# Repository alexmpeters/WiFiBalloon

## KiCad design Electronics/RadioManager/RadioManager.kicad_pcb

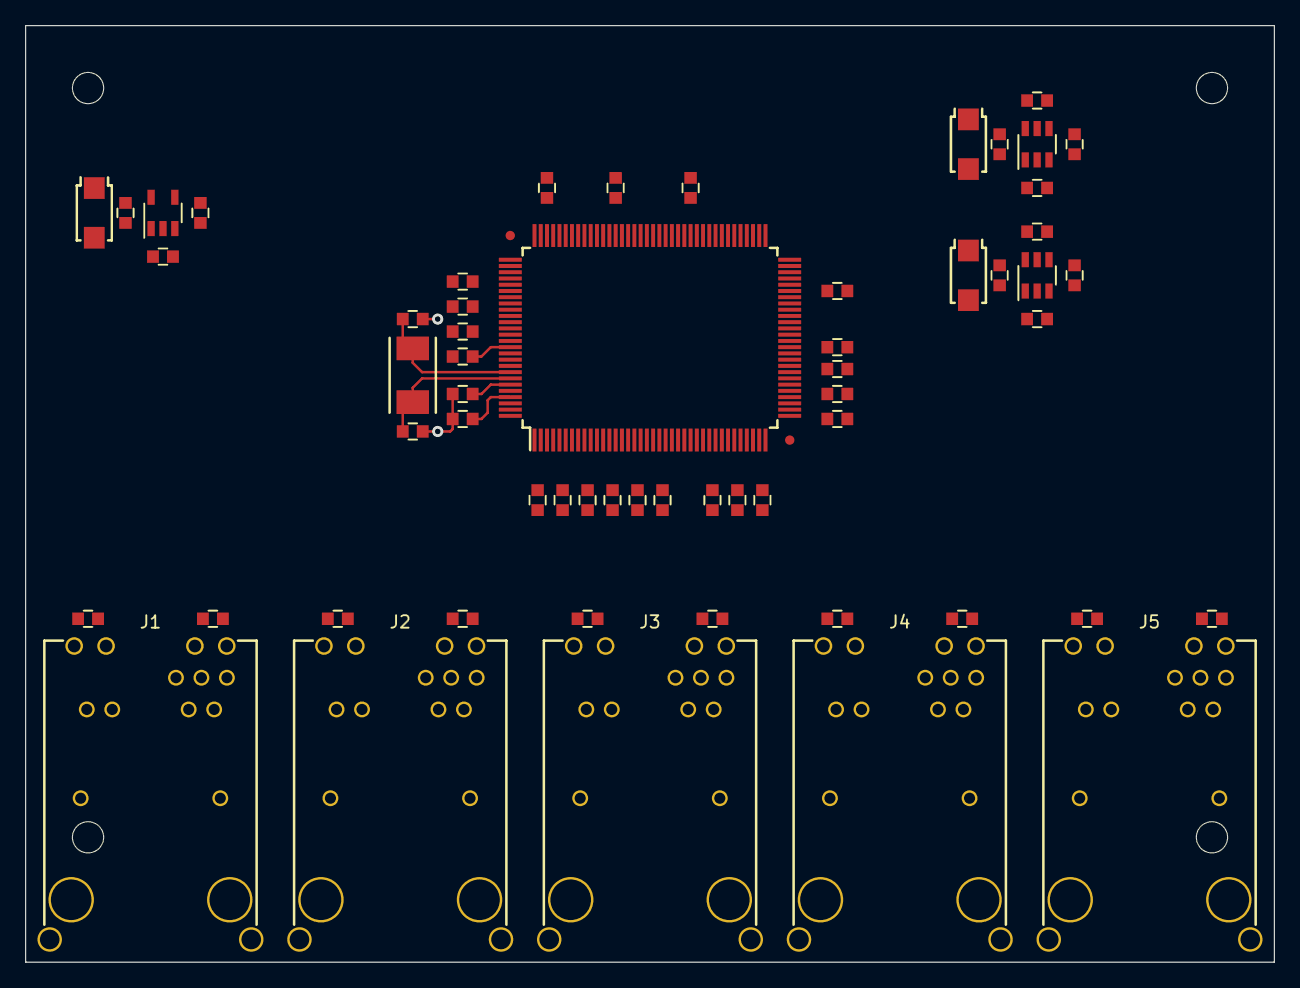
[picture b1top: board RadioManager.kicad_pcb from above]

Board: 2 copper layers, 100.0 x 75.0 mm, 63 parts (0 on the bottom side), 64 nets.

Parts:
C1, C2, C3, C4, C5, C6, C7, C8, C9, C10, C11, C12, C13, C14, C15, C16, C30: C; CAPC1608-N
C22, C23: 33pF; CAPC1608-N
C26, C27: 10000pF; CAPC1608-N
D1, D3, D4: CDBA140; SODFL5126-N
J1, J2, J3, J4, J5: RJ45-MAG-LED; CONN-0826-1L1T-57-F
MECH-JIG250, MECH-JIG250#2, MECH-JIG250#3, MECH-JIG250#4: VAL**; MECH-JIG250
R1, R2, R3, R10, R11, R16, R17, R18, R19, R20, R21, R22, R23, R24, R25: R; RESC1608-N
R4, R6, R7, R8, R9: 10k; RESC1608-N
R5: 3.01k; RESC1608-N
R12: 49.9k; RESC1608-N
R13: 15.8k; RESC1608-N
R14: 80.6k; RESC1608-N
R15: 64.2k; RESC1608-N
U1: KSZ8995FQI; QFP50P2320X1720-128N
U2: SC4503; SOT95P280-5N
U3, U4: AOZ1280; SOT95P280-6N
X1: 25MHz; XTAL-2SMD-60x35

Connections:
+1.8V: C1.1, C2.1, C4.1, C5.1, C7.1, C8.1, C10.1, C11.1, C13.1, C15.1, U1.3, U1.15, U1.31, U1.41, U1.43, U1.50, U1.89, U1.117, U1.123, U1.125
+3.3V: C3.1, C6.1, C9.1, C12.1, C14.1, C16.1, C30.1, J1.7, J2.7, J3.7, J4.7, J5.7, R4.2, R9.2, R12.2, R14.2, R16.1, R18.1, R20.1, R22.1, R24.1, U1.9, U1.18, U1.24, U1.37, U1.59, U1.77, U1.100
+24V: D1.2, J1.6, R2.2
+BATT: R10.1, R11.1, U2.5, U3.5, U4.5
/Switch/ACT1: R17.1, U1.104
/Switch/ACT2: R19.1, U1.101
/Switch/ACT3: R21.1, U1.96
/Switch/ACT4: R23.1, U1.93
/Switch/ACT5: R25.1, U1.90
/Switch/RXM1: J1.8, U1.8
/Switch/RXM2: J2.8, U1.14
/Switch/RXM3: J3.8, U1.23
/Switch/RXM4: J4.8, U1.29
/Switch/RXM5: J5.8, U1.36
/Switch/RXP1: J1.1, U1.7
/Switch/RXP2: J2.1, U1.13
/Switch/RXP3: J3.1, U1.22
/Switch/RXP4: J4.1, U1.28
/Switch/RXP5: J5.1, U1.35
/Switch/SPD1: J1.12, U1.106
/Switch/SPD2: J2.12, U1.103
/Switch/SPD3: J3.12, U1.98
/Switch/SPD4: J4.12, U1.95
/Switch/SPD5: J5.12, U1.92
/Switch/SW_EN: R4.1, U1.47
/Switch/TXM1: J1.9, U1.5
/Switch/TXM2: J2.9, U1.11
/Switch/TXM3: J3.9, U1.20
/Switch/TXM4: J4.9, U1.26
/Switch/TXM5: J5.9, U1.33
/Switch/TXP1: J1.2, U1.4
/Switch/TXP2: J2.2, U1.10
/Switch/TXP3: J3.2, U1.19
/Switch/TXP4: J4.2, U1.25
/Switch/TXP5: J5.2, U1.32
/Switch/XI: C22.1, U1.121, X1.1
/Switch/XO: C23.1, U1.122, X1.2
/Switch/~SW_RST: R9.1, U1.115
GND: C1.2, C2.2, C3.2, C4.2, C5.2, C6.2, C7.2, C8.2, C9.2, C10.2, C11.2, C12.2, C13.2, C14.2, C15.2, C16.2, C22.2, C23.2, C30.2, D3.1, D4.1, J1.11, J1.14, J2.11, J2.14, J3.11, J3.14, J4.11, J4.14, J5.11, J5.14, R3.1, R5.1, R6.1, R7.1, R8.1, R13.1, R15.1, U1.2, U1.6, U1.12, U1.16, U1.21, U1.27, U1.30, U1.34, U1.38, U1.39, U1.40, U1.42, U1.44, U1.49, U1.58, U1.76, U1.88, U1.99, U1.116, U1.124, U1.126, U1.127, U2.2, U3.2, U4.2
unnamed: J2.13, R18.2
unnamed: J2.15, R19.2
unnamed: J3.13, R20.2
unnamed: J3.15, R21.2
unnamed: J4.15, R23.2
unnamed: J4.13, R22.2
unnamed: J5.15, R25.2
unnamed: J5.13, R24.2
unnamed: J1.13, R16.2
unnamed: J1.15, R17.2
unnamed: R7.2, U1.114
unnamed: R8.2, U1.113
unnamed: R5.2, U1.17
unnamed: R6.2, U1.1
unnamed: R1.2, U2.4
unnamed: R11.2, U4.4
unnamed: C27.1, U4.1
unnamed: R14.1, R15.2, U4.3
unnamed: C27.2, D4.2, U4.6
unnamed: R2.1, R3.2, U2.3
unnamed: D1.1, U2.1
unnamed: R12.1, R13.2, U3.3
unnamed: R10.2, U3.4
unnamed: C26.2, D3.2, U3.6
unnamed: C26.1, U3.1

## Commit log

2014-07-21 :boom::camel: Added .gitattributes
2014-07-21 Add QFH simulation
2014-07-21 Add NEC logs and optimization directory to gitignore
2014-07-21 Parameterize QFH simulation
2014-07-24 Elevate QFH over ground
2014-07-24 Add helical antenna
2014-07-24 Add helix without match
2014-07-25 Add kicad project for switch/PoE injector
2014-07-25 Switch external interface placeholders
2014-08-04 Add Rocket M5 datasheet
2014-08-04 Add radio power skeleton
2014-08-04 Add switch datasheet and sheet
2014-09-10 Add actual RJ45 jacks
2014-09-11 Move power to new page
2014-09-11 Replace switch with industrial version
2014-09-11 Add kicad files to .gitignore
2014-09-11 Switch power connections
2014-09-11 Add port connections
2014-09-14 Wire RJ45 jacks
2014-09-14 Annotate existing components
2014-09-14 Add 3v3 and 1v8 supplies
2014-09-14 Switch support circuitry
2014-09-19 Associate major components
2014-09-21 Load new 3d models
2014-09-22 Add missing decoupling cap
2014-09-22 Connect LEDs
2014-09-22 Change backup file glob in gitignore
2014-10-02 Split sheath turnstile CAD
2014-10-02 Add jig and full assembly
2014-10-03 Change board form factor
2014-10-03 Swap tx/rx pairs for better routing
2014-10-04 Resonant crossed dipole simulation
2014-10-05 Resistor values
2014-10-08 Fix offset on jig saw guide
2014-10-08 Change dimensions for design intent
2014-10-08 Update to correct balun slot width
2014-10-08 Add RP-SMA jack
2014-10-08 Update element lengths for new center conductor
2014-10-08 Update tube lengths for reflector spacing
    3/8 wave from front surface of jack
2014-10-08 Update and add radome to antenna assembly
2014-10-08 Remove temp files
2014-11-07 Add Ubiquiti configuration manual
2014-11-14 Generic 5.8GHz crossed dipole
2014-11-14 Update boards for fabrication
